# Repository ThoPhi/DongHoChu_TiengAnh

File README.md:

DongHoChu_TiengAnh
==================

Đồng hồ thay vì hiện số, bây giờ nó sẽ như một người bạn thông báo giờ bằng ngôn ngữ, tiếng Anh.
Tên gọi khác Dough Word Clock 

*Nguyên liệu
1. Arduino Pro mini 
2. led dây cắt khúc 
3. Module RTC 
4. Mạch mở rộng SPI-Paralell 595

* Các cụm từ: 
1. It's 
2. One
3. Two
4. Three 
5. Four 
6. Five 
7. Six 
8. Seven
9. Eight
10. Nine
11. Ten
12. Eleven 
13. Twelve 
14. quater 
15. half
16. to
17. past 
18. o'clock

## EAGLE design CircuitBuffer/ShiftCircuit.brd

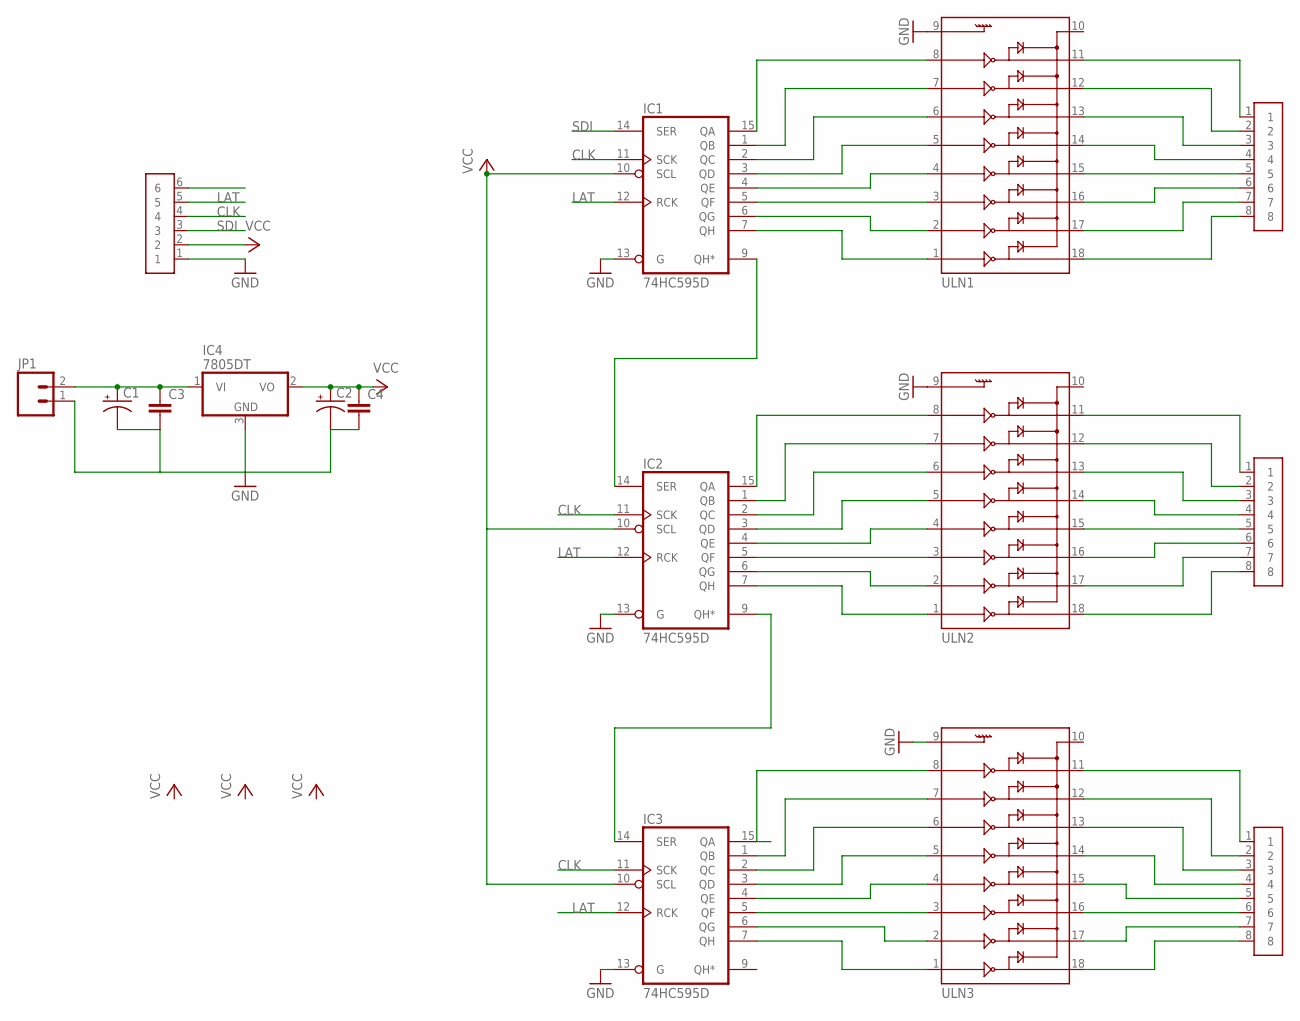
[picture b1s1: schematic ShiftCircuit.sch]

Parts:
C1, C2: CAP_POL1206; EIA3216
C3, C4: C-EUC0805; C0805
IC1, IC2, IC3: 74HC595D; SO16
IC4: 7805DT; TO252
JP1: M02PTH4; 1X02_XTRA_BIG
U$1, U$2, U$3: HEADER8
U$4: HEADER6
ULN1, ULN2, ULN3: ULN2803SOICW; SO18L

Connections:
CLK: IC1.11 (SCK), IC2.11 (SCK), IC3.11 (SCK), U$4.4
GND: C1.C (-), C2.C (-), C3.2, C4.2, IC1.8 (GND), IC1.13 (G), IC2.8 (GND), IC2.13 (G), IC3.8 (GND), IC3.13 (G), IC4.3 (GND), JP1.1, U$4.1, ULN1.9, ULN2.9, ULN3.9
LAT: IC1.12 (RCK), IC2.12 (RCK), IC3.12 (RCK), U$4.5
unnamed: IC1.15 (QA), ULN1.8
unnamed: IC1.1 (QB), ULN1.7
unnamed: IC1.2 (QC), ULN1.6
unnamed: IC1.3 (QD), ULN1.5
unnamed: IC1.4 (QE), ULN1.4
unnamed: IC1.5 (QF), ULN1.3
unnamed: IC1.6 (QG), ULN1.2
unnamed: IC1.7 (QH), ULN1.1
unnamed: IC1.9 (QH*), IC2.14 (SER)
unnamed: C1.A (+), C3.1, IC4.1 (VI), JP1.2
unnamed: IC2.15 (QA), ULN2.8
unnamed: IC2.1 (QB), ULN2.7
unnamed: IC2.2 (QC), ULN2.6
unnamed: IC2.3 (QD), ULN2.5
unnamed: IC2.4 (QE), ULN2.4
unnamed: IC2.9 (QH*), IC3.14 (SER)
unnamed: IC2.5 (QF), ULN2.3
unnamed: IC2.6 (QG), ULN2.2
unnamed: IC2.7 (QH), ULN2.1
unnamed: IC3.5 (QF), ULN3.3
unnamed: IC3.1 (QB), ULN3.7
unnamed: IC3.2 (QC), ULN3.6
unnamed: IC3.3 (QD), ULN3.5
unnamed: IC3.4 (QE), ULN3.4
unnamed: U$1.1, ULN1.11
unnamed: IC3.7 (QH), ULN3.1
unnamed: U$1.3, ULN1.13
unnamed: U$1.4, ULN1.14
unnamed: U$1.5, ULN1.15
unnamed: U$1.6, ULN1.16
unnamed: IC3.15 (QA), ULN3.8
unnamed: U$2.4, ULN2.14
unnamed: U$2.5, ULN2.15
unnamed: U$2.6, ULN2.16
unnamed: U$2.7, ULN2.17
unnamed: U$3.1, ULN3.11
unnamed: IC3.6 (QG), ULN3.2
unnamed: U$3.2, ULN3.12
unnamed: U$3.3, ULN3.13
unnamed: U$1.2, ULN1.12
unnamed: U$3.4, ULN3.14
unnamed: U$3.5, ULN3.15
unnamed: U$3.6, ULN3.16
unnamed: U$3.7, ULN3.17
unnamed: U$3.8, ULN3.18
unnamed: U$1.7, ULN1.17
unnamed: U$2.1, ULN2.11
unnamed: U$2.2, ULN2.12
unnamed: U$2.3, ULN2.13
unnamed: U$1.8, ULN1.18
unnamed: U$2.8, ULN2.18
SDI: IC1.14 (SER), U$4.3
VCC: C2.A (+), C4.1, IC1.10 (SCL), IC1.16 (VCC), IC2.10 (SCL), IC2.16 (VCC), IC3.10 (SCL), IC3.16 (VCC), IC4.2 (VO), U$4.2

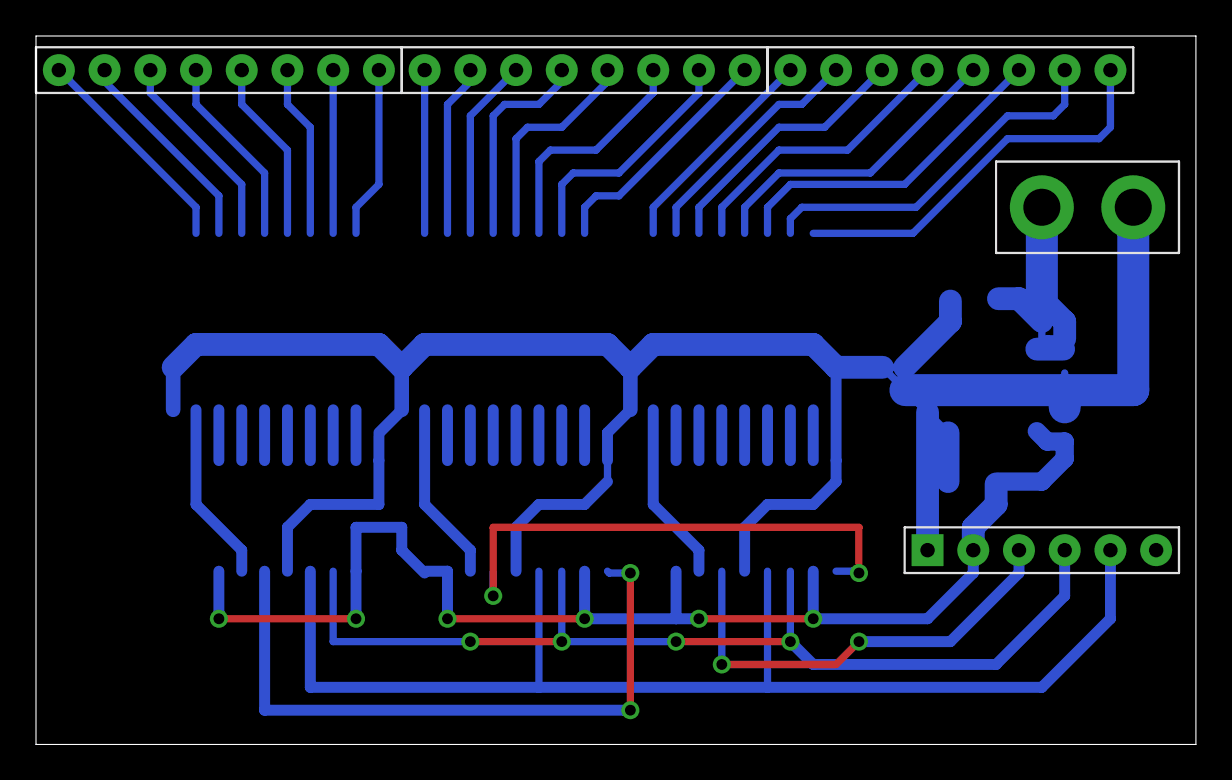
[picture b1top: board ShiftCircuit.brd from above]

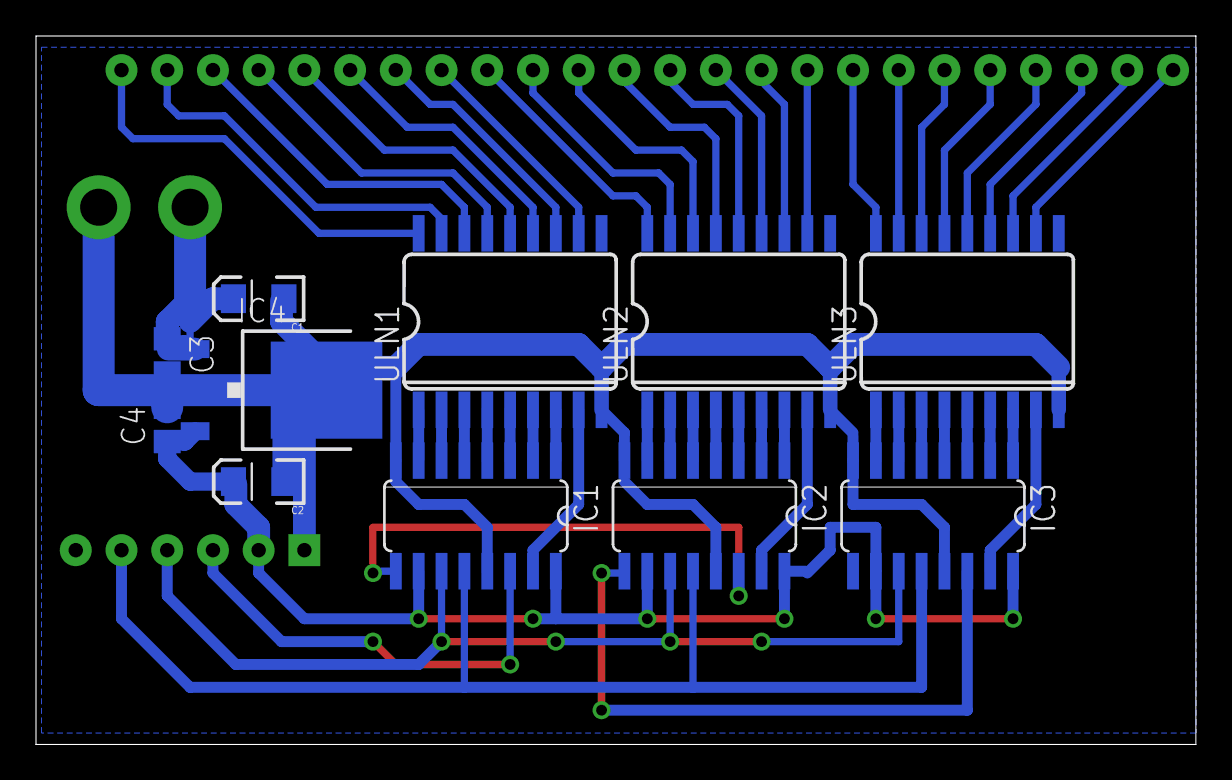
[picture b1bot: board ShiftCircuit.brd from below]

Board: 2 copper layers, 64.4 x 39.4 mm, 16 parts (11 on the bottom side), 56 nets.

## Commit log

2015-01-05 add code
2015-01-05 add files
